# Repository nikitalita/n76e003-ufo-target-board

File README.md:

# N76e003 UFO Target board for the Chipwhisper UFO board

Tested and working, gerbers are in `jlcpcb/`

# Note
ChipWhisperer normally has gpio1 set as serial_rx and gpio1 set as serial_tx; v1.1 and earlier of this board had this reversed. v1.2 and later fixes this issue. When using these earilier boards, just set:
```python
scope.io.tio1 = "serial_tx"
scope.io.tio2 = "serial_rx"
```

The shunt resistor value is 22R, which is likely too high, given that the max current is 3.9mA operating at 16mhz. I have not had a chance to test additional shunt resistor values, but I would recommend using a lower value, such as 11R.

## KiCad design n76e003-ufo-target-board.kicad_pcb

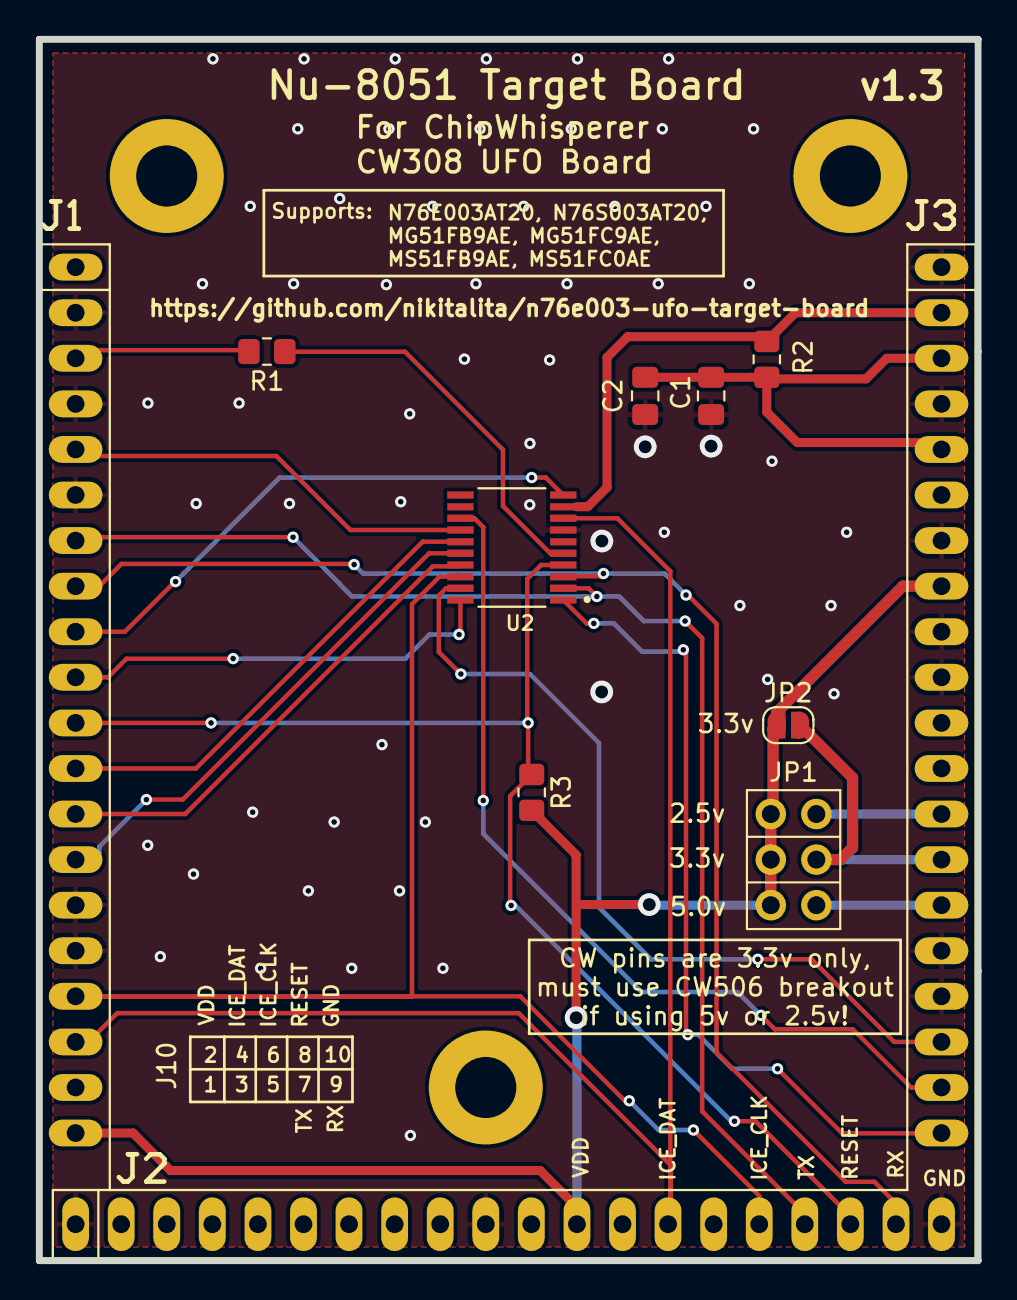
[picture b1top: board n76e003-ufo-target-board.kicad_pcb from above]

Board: 2 copper layers, 52.3 x 68.1 mm, 9 parts (0 on the bottom side), 23 nets.

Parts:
C1: 100nF; C_0805_2012Metric_Pad1.18x1.45mm_HandSolder
C2: 2.2uF (OPT); C_0805_2012Metric_Pad1.18x1.45mm_HandSolder
J1: CW308T_CONNBOARD
JP1: Jumper_2_Open; PinHeader_2x03_P2.54mm_Vertical
JP2: SolderJumper_2_Open; SolderJumper-2_P1.3mm_Open_RoundedPad1.0x1.5mm
R1: 100R; R_0805_2012Metric_Pad1.20x1.40mm_HandSolder
R2: 51R; R_0805_2012Metric_Pad1.20x1.40mm_HandSolder
R3: 10K; R_0805_2012Metric_Pad1.20x1.40mm_HandSolder
U2: N76E003AT20; SOP65P640X120-20N

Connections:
+2V5: J1.C13 (VCC2.5V), JP1.2 (B1)
+3.3V: J1.C14 (VCC3.3V), JP1.4 (B2), JP2.2 (B)
+5V: J1.C15 (VCC5.0V), JP1.6 (B3)
CLK: R1.1, U2.5 (P3.0/~INT0/OSCIN/AIN1)
CLKOUT: J1.A5 (CLKIN), U2.14 (P1.1/PWM1/IC1/AIN7/CLO)
GND: C1.2, C2.2, J1.A2 (GND), J1.A4 (GND), J1.A6 (GND), J1.A15 (GND), J1.A16 (GND), J1.B1 (GND), J1.B10 (GND), J1.B20 (HDR10), J1.C1 (GND), J1.C4 (GND), J1.C7 (GND), J1.C9 (GND), J1.C10 (GND), J1.C16 (GND), J1.C17 (GND), U2.7 (GND)
GPI01: J1.A7 (GPIO1), J1.B17 (HDR7), U2.2 (P0.6/TXD/AIN3)
GPI02: J1.A8 (GPIO2), J1.B19 (HDR9), U2.3 (P0.7/RXD/AIN2)
GPI03: J1.A9 (GPIO3), U2.10 (P1.5/PWM5/IC7/~SS)
GPI04: J1.A10 (GPIO4), U2.20 (P0.4/AIN5/STADC/PWM3/IC3)
LED1: J1.C18 (LED1), U2.19 (P0.3/PWM5/IC5/AIN6)
LED2: J1.C19 (LED2), U2.13 (P1.2/PWM0/IC0)
LED3: J1.C20 (LED3), U2.1 (P0.5/PWM2/IC6/T0/AIN4)
MISO: J1.A13 (MISO), U2.17 (P0.1/PWM4/IC4/MISO)
MOSI: J1.A14 (MOSI), U2.16 (P0.0/PWM3/IC3/MOSI/T1)
unnamed: J1.A3 (CLKOUT), R1.2
unnamed: C1.1, C2.1, J1.C3 (SHUNTH), J1.C5 (FILT_LP), R2.2
PDIC: J1.A17 (PDIC), J1.B16 (HDR6), U2.18 (P0.2/ICPCK/OCDCK/RXD_1/[SCL])
PDID: J1.A18 (PDID), J1.B14 (HDR4), U2.8 (P1.6/[SDA]/TXD_1/ICPDA/OCDDA)
RST: J1.A11 (NRST), J1.B18 (HDR8), R3.2, U2.4 (P2.0/~RST)
SCK: J1.A12 (SCK), U2.15 (P1.0/PWM2/IC2/SPCLK)
VBUS: J1.C2 (SHUNTL), R2.1, U2.9 (VDD)
VCC: J1.A20 (VREF), J1.B12 (HDR2), J1.C8 (FILTIN), JP1.1 (A1), JP1.3 (A2), JP1.5 (A3), JP2.1 (A), R3.1

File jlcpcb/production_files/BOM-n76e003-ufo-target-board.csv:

Comment,Designator,Footprint,LCSC
100R,R1,R_0805_2012Metric_Pad1.20x1.40mm_HandSolder,C17408
10K,R3,R_0805_2012Metric_Pad1.20x1.40mm_HandSolder,C17414
51R,R2,R_0805_2012Metric_Pad1.20x1.40mm_HandSolder,C17738
100nF,C1,C_0805_2012Metric_Pad1.18x1.45mm_HandSolder,C49678
N76E003AT20,U2,SOP65P640X120-20N,C82751
CW308T_CONNBOARD,J1,CW308T_CONNBOARD,
Jumper_2_Open,JP1,PinHeader_2x03_P2.54mm_Vertical,
SolderJumper_2_Open,JP2,SolderJumper-2_P1.3mm_Open_RoundedPad1.0x1.5mm,

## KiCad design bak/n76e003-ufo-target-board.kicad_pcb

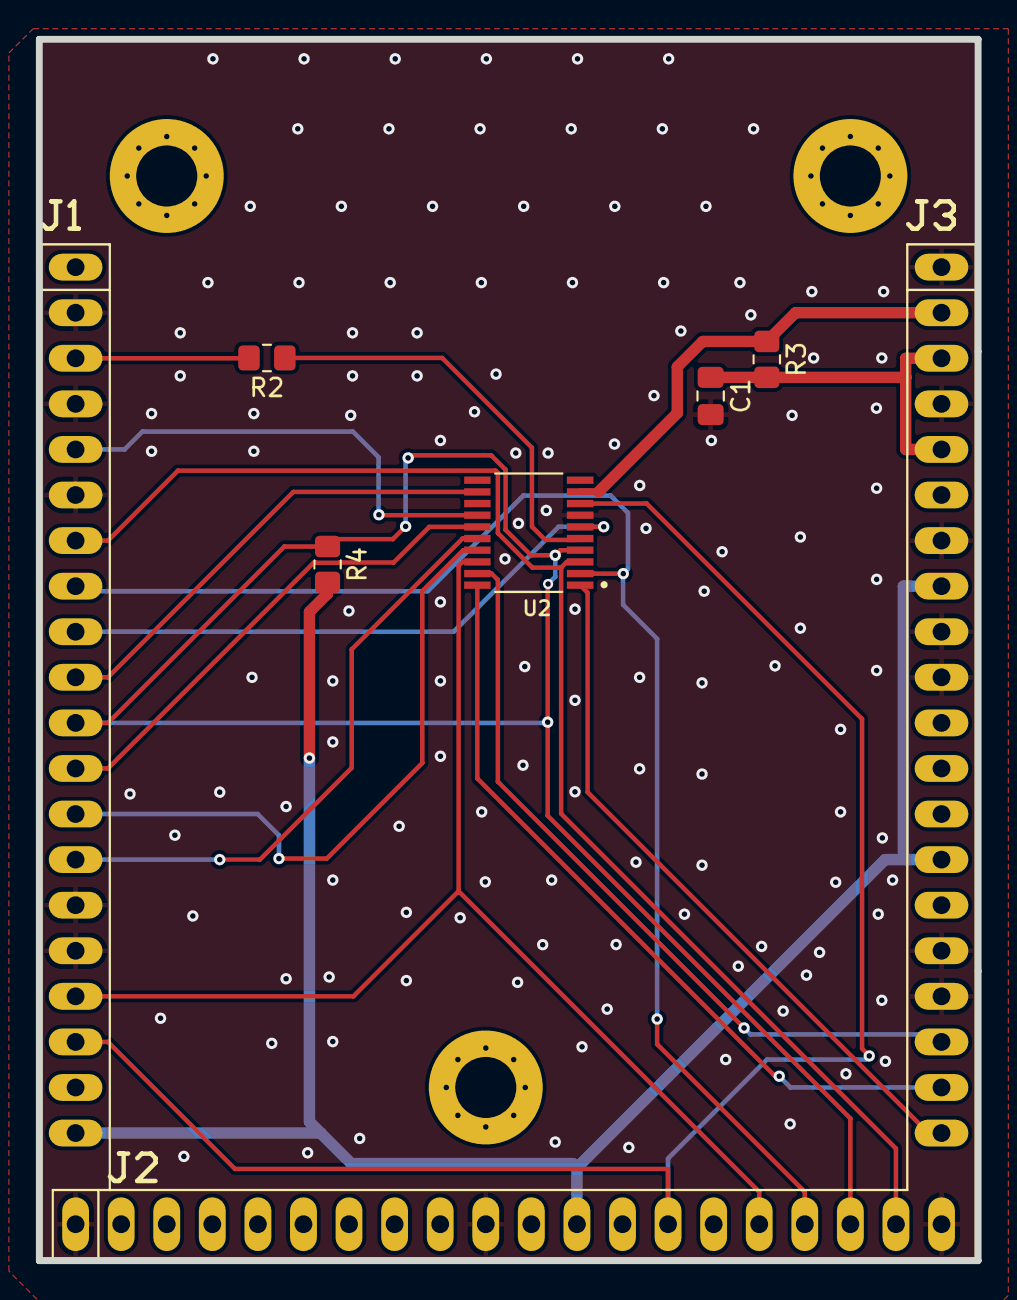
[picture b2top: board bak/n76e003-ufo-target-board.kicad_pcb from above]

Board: 2 copper layers, 52.3 x 68.1 mm, 6 parts (0 on the bottom side), 20 nets.

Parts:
C1: 100nF; C_0805_2012Metric_Pad1.18x1.45mm_HandSolder
J1: >VALUE; CW308T_CONNBOARD
R2: 100R; R_0805_2012Metric_Pad1.20x1.40mm_HandSolder
R3: 51R; R_0805_2012Metric_Pad1.20x1.40mm_HandSolder
R4: 10K; R_0805_2012Metric_Pad1.20x1.40mm_HandSolder
U2: N76E003AT20; SOP65P640X120-20N

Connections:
CLK: R2.1, U2.5 (P3.0/~INT0/OSCIN/AIN1)
CLKOUT: J1.A5 (CLKIN), U2.14 (P1.1/PWM1/IC1/AIN7/CLO)
GND: C1.2, J1.A2 (GND), J1.A4 (GND), J1.A6 (GND), J1.A15 (GND), J1.A16 (GND), J1.B1 (GND), J1.B10 (GND), J1.B20 (HDR10), J1.C1 (GND), J1.C4 (GND), J1.C7 (GND), J1.C9 (GND), J1.C10 (GND), J1.C16 (GND), J1.C17 (GND), U2.7 (GND)
GPI01: J1.A7 (GPIO1), J1.B19 (HDR9), U2.3 (P0.7/RXD/AIN2)
GPI02: J1.A8 (GPIO2), J1.B17 (HDR7), U2.2 (P0.6/TXD/AIN3)
GPI03: J1.A9 (GPIO3), U2.6 (P1.7/~INT1/AIN0)
GPI04: J1.A10 (GPIO4), U2.12 (P1.3/SCL/[STADC])
LED1: J1.C18 (LED1), U2.19 (P0.3/PWM5/IC5/AIN6)
LED2: J1.C19 (LED2), U2.20 (P0.4/AIN5/STADC/PWM3/IC3)
LED3: J1.C20 (LED3), U2.1 (P0.5/PWM2/IC6/T0/AIN4)
MISO: J1.A13 (MISO), U2.17 (P0.1/PWM4/IC4/MISO)
MOSI: J1.A14 (MOSI), U2.16 (P0.0/PWM3/IC3/MOSI/T1)
unnamed: J1.A3 (CLKOUT), R2.2
unnamed: C1.1, J1.C3 (SHUNTH), J1.C5 (FILT_LP), R3.2
PDIC: J1.A17 (PDIC), J1.B16 (HDR6), U2.18 (P0.2/ICPCK/OCDCK/RXD_1/[SCL])
PDID: J1.A18 (PDID), J1.B14 (HDR4), U2.8 (P1.6/[SDA]/TXD_1/ICPDA/OCDDA)
RST: J1.A11 (NRST), J1.B18 (HDR8), R4.1, U2.4 (P2.0/~RST)
SCK: J1.A12 (SCK), U2.15 (P1.0/PWM2/IC2/SPCLK)
VBUS: J1.C2 (SHUNTL), R3.1, U2.9 (VDD)
VCC: J1.A20 (VREF), J1.B12 (HDR2), J1.C8 (FILTIN), J1.C14 (VCC3.3V), R4.2

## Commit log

2024-03-11 Remove C2, add url to board
2024-03-11 add note
2024-03-11 fix note, add license
2024-03-11 remove through-holes on mounting holes
    Not necessary, adds cost to board
2024-03-17 remove old backups
2024-03-17 add datasheet
2024-03-17 switch gpio1 and gpio2 lines, update gerbers, notes
2024-03-17 add C2 footprint back, exclude from BOM by default
2024-04-01 Add reference docs
2024-04-01 v1.3
    Remove GPIO4 connect header, bump shunt resistor value to 51R, update on-board notes
